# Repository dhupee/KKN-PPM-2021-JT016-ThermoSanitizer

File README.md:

# KKN-PPM-2021-JT016-ThermoSanitizer

test adding readme from branch, im learning a bit now okay
add abit more

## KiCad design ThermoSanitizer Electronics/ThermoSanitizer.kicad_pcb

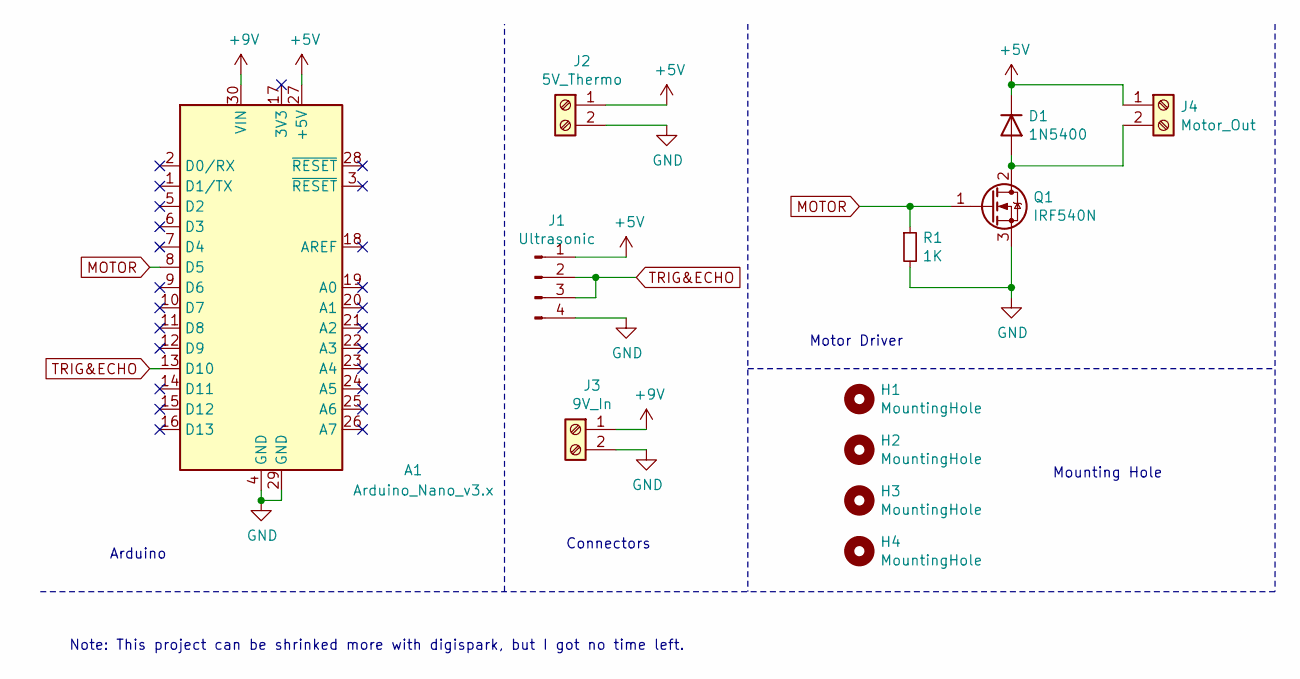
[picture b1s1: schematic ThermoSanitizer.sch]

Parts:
A1: Arduino_Nano_v3.x; Arduino_Nano
D1: 1N5400; D_DO-201AD_P15.24mm_Horizontal
H1, H2, H3, H4: MountingHole; MountingHole_3.2mm_M3
J1: Ultrasonic; PinSocket_1x04_P2.54mm_Horizontal
J2: 5V_Thermo; TerminalBlock_bornier-2_P5.08mm
J3: 9V_In; TerminalBlock_bornier-2_P5.08mm
J4: Motor_Out; TerminalBlock_bornier-2_P5.08mm
Q1: IRF540N; TO-220-3_Vertical
R1: 1K; R_Axial_DIN0207_L6.3mm_D2.5mm_P2.54mm_Vertical

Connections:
+5V: A1.27 (+5V), D1.1 (K), J1.1, J2.1, J4.1
+9V: A1.30 (VIN), J3.1
GND: A1.4 (GND), A1.29 (GND), J1.4, J2.2, J3.2, Q1.3 (S), R1.2
MOTOR: A1.8 (D5), Q1.1 (G), R1.1
unnamed: D1.2 (A), J4.2, Q1.2 (D)
TRIG&ECHO: A1.13 (D10), J1.2, J1.3

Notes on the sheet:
Arduino
Motor Driver
Mounting Hole
Connectors
Note: This project can be shrinked more with digispark, but I got no time left.

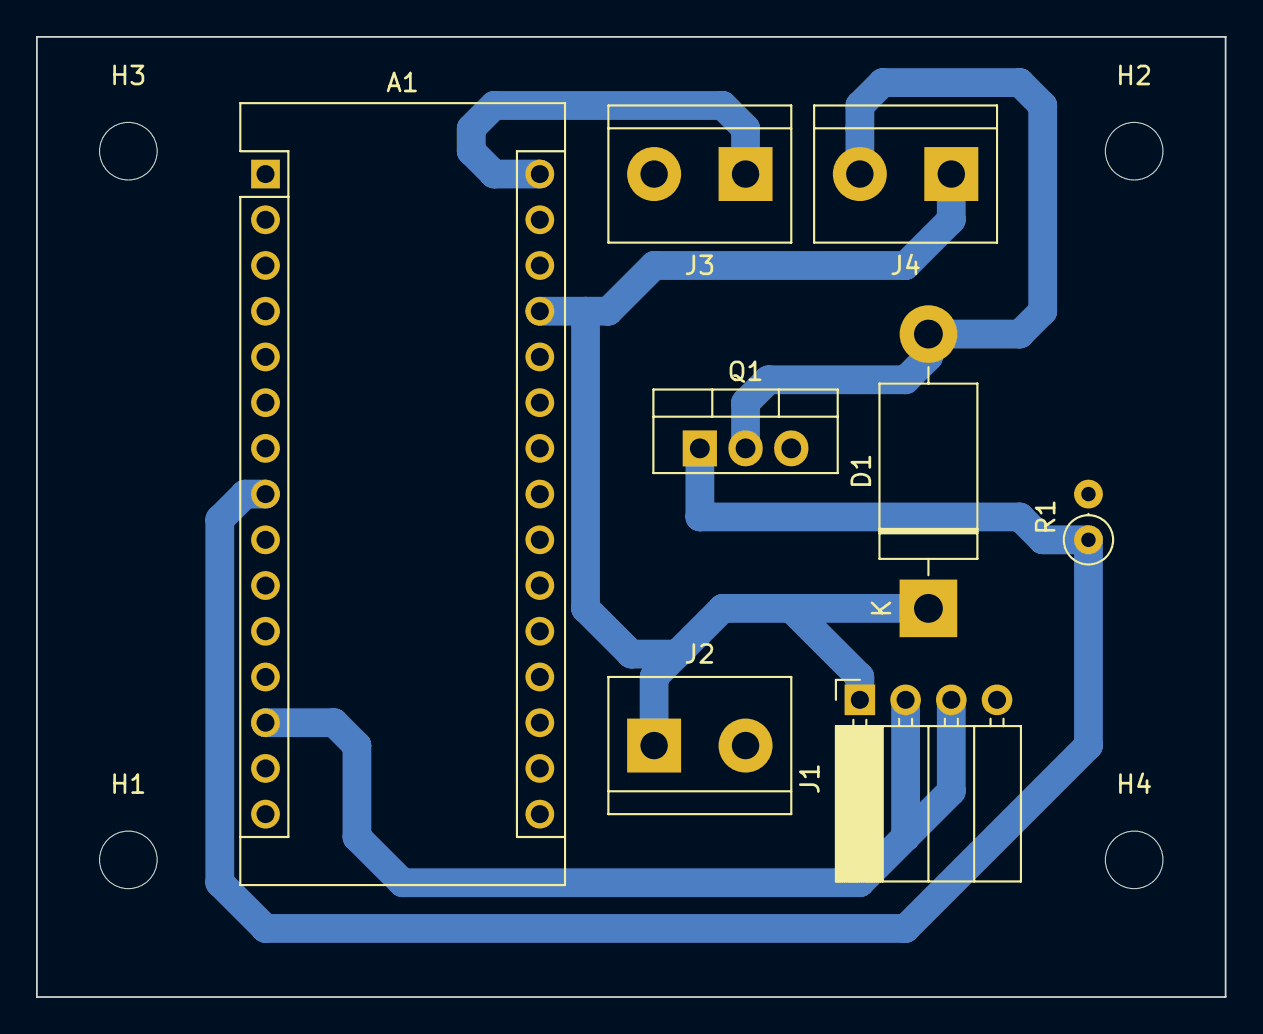
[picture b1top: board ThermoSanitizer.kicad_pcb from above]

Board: 2 copper layers, 66.0 x 53.3 mm, 12 parts (0 on the bottom side), 6 nets.

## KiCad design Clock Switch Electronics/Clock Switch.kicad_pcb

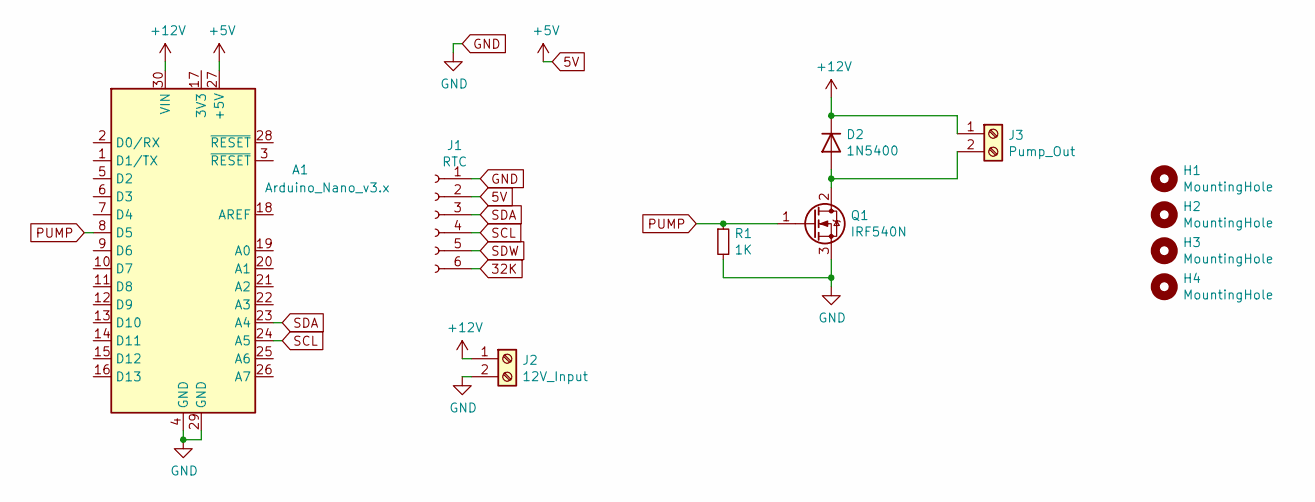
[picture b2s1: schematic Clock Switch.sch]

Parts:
A1: Arduino_Nano_v3.x; Arduino_Nano
D2: 1N5400; D_DO-201AD_P15.24mm_Horizontal
H1, H2, H3, H4: MountingHole; MountingHole_3.2mm_M3
J1: RTC; PinSocket_1x06_P2.54mm_Vertical
J2: 12V_Input; TerminalBlock_bornier-2_P5.08mm
J3: Pump_Out; TerminalBlock_bornier-2_P5.08mm
Q1: IRF540N; TO-220-3_Vertical
R1: 1K; R_Axial_DIN0207_L6.3mm_D2.5mm_P2.54mm_Vertical

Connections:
5V: A1.27 (+5V), J1.2
32K: J1.6
+12V: A1.30 (VIN), D2.1 (K), J2.1, J3.1
GND: A1.4 (GND), A1.29 (GND), J1.1, J2.2, Q1.3 (S), R1.2
unnamed: D2.2 (A), J3.2, Q1.2 (D)
PUMP: A1.8 (D5), Q1.1 (G), R1.1
SCL: A1.24 (A5), J1.4
SDA: A1.23 (A4), J1.3
SDW: J1.5

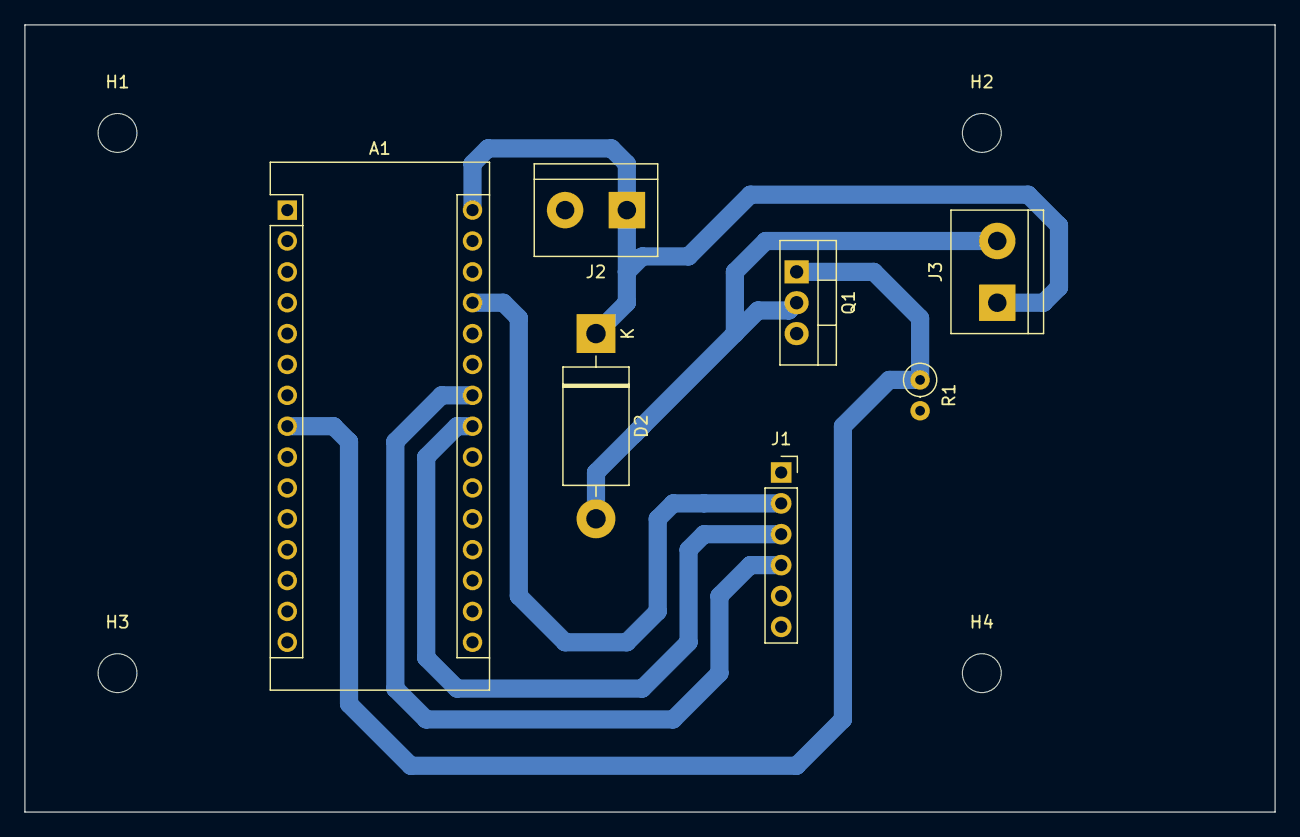
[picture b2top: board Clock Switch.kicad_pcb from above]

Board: 2 copper layers, 102.9 x 64.8 mm, 11 parts (0 on the bottom side), 7 nets.

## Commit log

2021-07-21 design pcb
2021-07-21 test revert
2021-07-21 Revert "design pcb"
    This reverts commit ee3a990a2a356cba129a6f2256962307c95830fc.
2021-07-21 revert to 'design pcb'
2021-07-25 edit pcb
2021-07-25 change folder name
2021-08-04 add invoice and canva project
2021-08-07 add clock switch
2021-08-07 Adding alot of stuff
2021-08-08 add 3d print gcode
2021-08-20 add a lot of stuff
2021-11-11 Finally
